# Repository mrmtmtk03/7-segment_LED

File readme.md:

# 7セグメントLED回路
## 回路構成
KiCadにて回路図を作成した。
7セグメントデコーダー([TC4511BP](https://toshiba.semicon-storage.com/jp/semiconductor/product/general-purpose-logic-ics/detail.TC4511BP.html))を使用して、4つの7セグメントLEDをArduino UNOによりダイナミック点灯する回路である。

## 使用部品
使用する7セグメントLEDはカソードコモンで、データシートより順方向電圧$`V_F=3.5\,[\mathrm{V}]`$、順方向電流の絶対最大定格は$`I_F=35\,[\mathrm{mA}]`$である。
今回は$`I_F=4.5\,[\mathrm{mA}]`$となるように抵抗1を選定し以下のようにRを330 Ωと定める。
```math
R_1=\frac{V-V_F}{I_F}=\frac{5-3.5}{0.0045}≒330\,[\mathrm{Ω}]
```
具体的な使用部品は以下の表に示す。
| 部品                         | 型番         |                   秋月電子販売コード                   |
| :--------------------------- | :----------- | :----------------------------------------------------: |
| 7セグメントドライバー        | TC4511BP     | [114057](https://akizukidenshi.com/catalog/g/g114057/) |
| 7セグメントLED               | OSL10391-LRA | [130319](https://akizukidenshi.com/catalog/g/g130319/) |
| 抵抗器                       | 330 Ω        | [107812](https://akizukidenshi.com/catalog/g/g107812/) |
| 丸ピンICソケット(16P)        | 2227MC-16-03 | [100029](https://akizukidenshi.com/catalog/g/g100029/) |
| 細ピンヘッダー(オスL型) 1×12 | PHA-1x12RG   | [111573](https://akizukidenshi.com/catalog/g/g111573/) |

なお、点灯させるためには、この他に[Arduino UNO](https://akizukidenshi.com/catalog/g/g115574/)が必要である。
## プリント基板の作成
設計した基板データは本リポジトリで公開している。
例えば、[JLCPCB](https://jlcpcb.com/)であればこの[ZIPファイル](7-segment_LED_02_kicad\production\7-segment_LED_02_kicad.zip) `7-segment_LED_02_kicad\production\7-segment_LED_02_kicad.zip`をgerber fileとしてアップロードすることで基板の発注ができる。

ただし、基板の発注内容に誤りがあった場合、その結果生じた発注者の不利益について、当方は責任を負いかねますので、十分ご注意ください。

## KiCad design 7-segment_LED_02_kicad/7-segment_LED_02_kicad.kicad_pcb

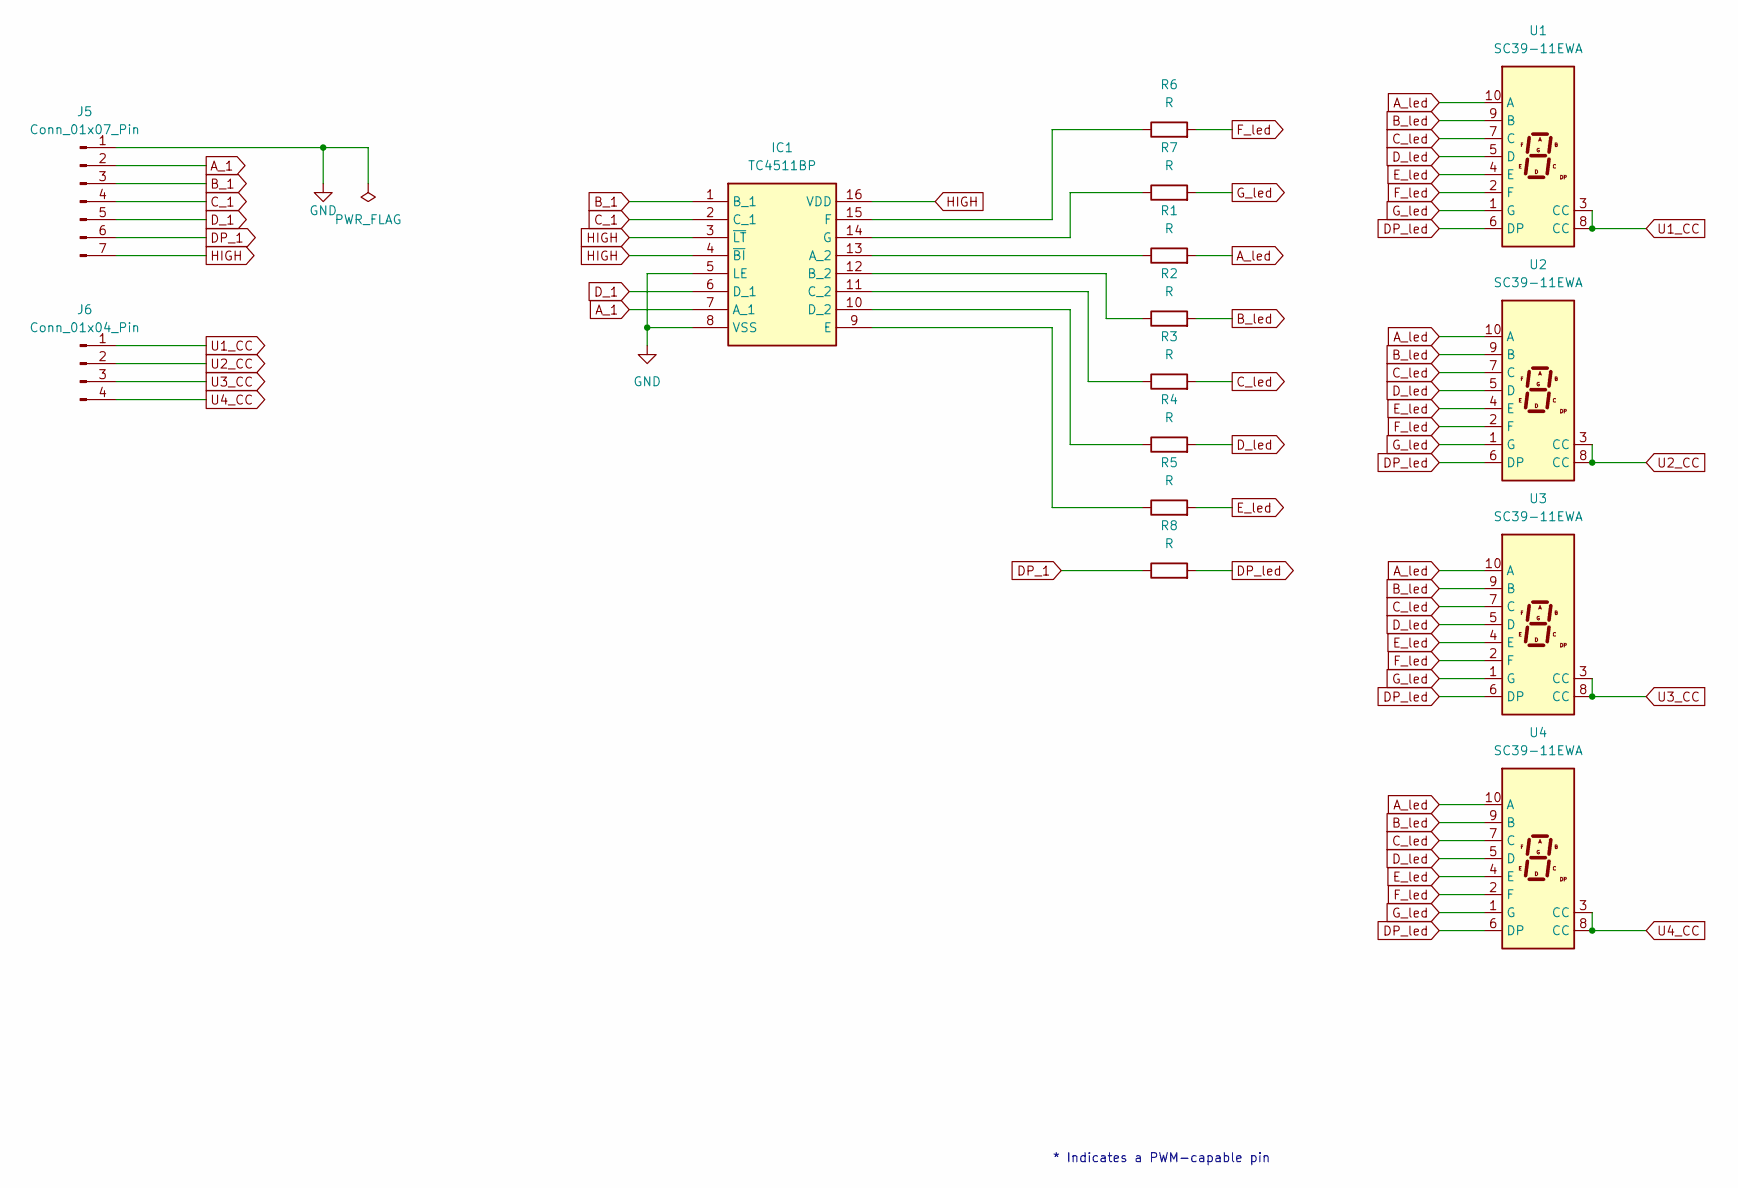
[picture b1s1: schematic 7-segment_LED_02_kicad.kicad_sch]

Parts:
IC1: TC4511BP; DIP762W60P254L1975H445Q16N; Manufacturer_Part_Number TC4511BP; Mouser Part Number N/A
J5: Conn_01x07_Pin; PinHeader_1x07_P2.54mm_Vertical
J6: Conn_01x04_Pin; PinHeader_1x04_P2.54mm_Vertical
R1, R2, R3, R4, R5, R6, R7, R8: R; R_Axial_DIN0207_L6.3mm_D2.5mm_P10.16mm_Horizontal
U1, U2, U3, U4: SC39-11EWA; Sx39-1xxxxx

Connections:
A_1: IC1.7 (A_1), J5.2; also elsewhere on the board
A_led: R1.2, U1.10 (A), U2.10 (A), U3.10 (A), U4.10 (A)
B_1: IC1.1 (B_1), J5.3; also elsewhere on the board
B_led: R2.2, U1.9 (B), U2.9 (B), U3.9 (B), U4.9 (B)
C_1: IC1.2 (C_1), J5.4; also elsewhere on the board
C_led: R3.2, U1.7 (C), U2.7 (C), U3.7 (C), U4.7 (C)
DP_1: J5.6, R8.1; also elsewhere on the board
DP_led: R8.2, U1.6 (DP), U2.6 (DP), U3.6 (DP), U4.6 (DP)
D_1: IC1.6 (D_1), J5.5; also elsewhere on the board
D_led: R4.2, U1.5 (D), U2.5 (D), U3.5 (D), U4.5 (D)
E_led: R5.2, U1.4 (E), U2.4 (E), U3.4 (E), U4.4 (E)
F_led: R6.2, U1.2 (F), U2.2 (F), U3.2 (F), U4.2 (F)
GND: IC1.5 (LE), IC1.8 (VSS), J5.1; also elsewhere on the board
G_led: R7.2, U1.1 (G), U2.1 (G), U3.1 (G), U4.1 (G)
HIGH: IC1.3 (~LT), IC1.4 (~BI), IC1.16 (VDD), J5.7; also elsewhere on the board
unnamed: IC1.13 (A_2), R1.1
unnamed: IC1.12 (B_2), R2.1
unnamed: IC1.11 (C_2), R3.1
unnamed: IC1.10 (D_2), R4.1
unnamed: IC1.9 (E), R5.1
unnamed: IC1.15 (F), R6.1
unnamed: IC1.14 (G), R7.1
U1_CC: J6.1, U1.3 (CC), U1.8 (CC)
U2_CC: J6.2, U2.3 (CC), U2.8 (CC)
U3_CC: J6.3, U3.3 (CC), U3.8 (CC)
U4_CC: J6.4, U4.3 (CC), U4.8 (CC)

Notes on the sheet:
* Indicates a PWM-capable pin

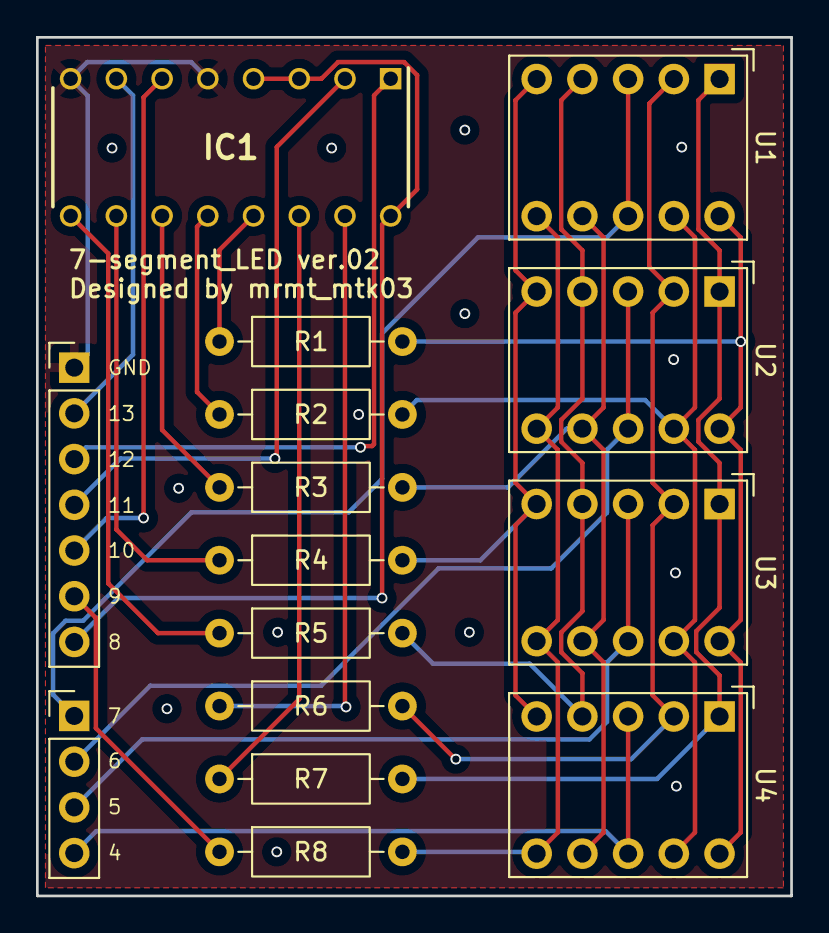
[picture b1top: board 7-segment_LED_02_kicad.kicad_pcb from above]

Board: 2 copper layers, 41.9 x 47.7 mm, 15 parts (0 on the bottom side), 26 nets.

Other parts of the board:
GND: Conn_01x07_Pin; PinHeader_1x07_P2.54mm_Vertical

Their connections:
A_1: GND.2; also elsewhere on the board
B_1: GND.3; also elsewhere on the board
C_1: GND.4; also elsewhere on the board
DP_1: GND.6; also elsewhere on the board
D_1: GND.5; also elsewhere on the board
GND: GND.1; also elsewhere on the board
HIGH: GND.7; also elsewhere on the board

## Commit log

2025-09-05 7-segment_LEDをアップロード
2025-09-05 HOWtoBUILD.mdの組み立て手順を整理し、説明を追加
2025-09-07 Update HOWtoBUILD.md
    プログラムの書き込みについて修正
2025-09-07 組み立て画像を追加
2025-09-07 サンプルプログラム解説セクションを追加
2025-09-07 サンプルプログラム解説を作成予定として追記
2025-09-07 build_plug.jpgの更新
2025-09-30 readme.mdを作成
2025-10-10 プリント基板の作成に関する情報を追加
